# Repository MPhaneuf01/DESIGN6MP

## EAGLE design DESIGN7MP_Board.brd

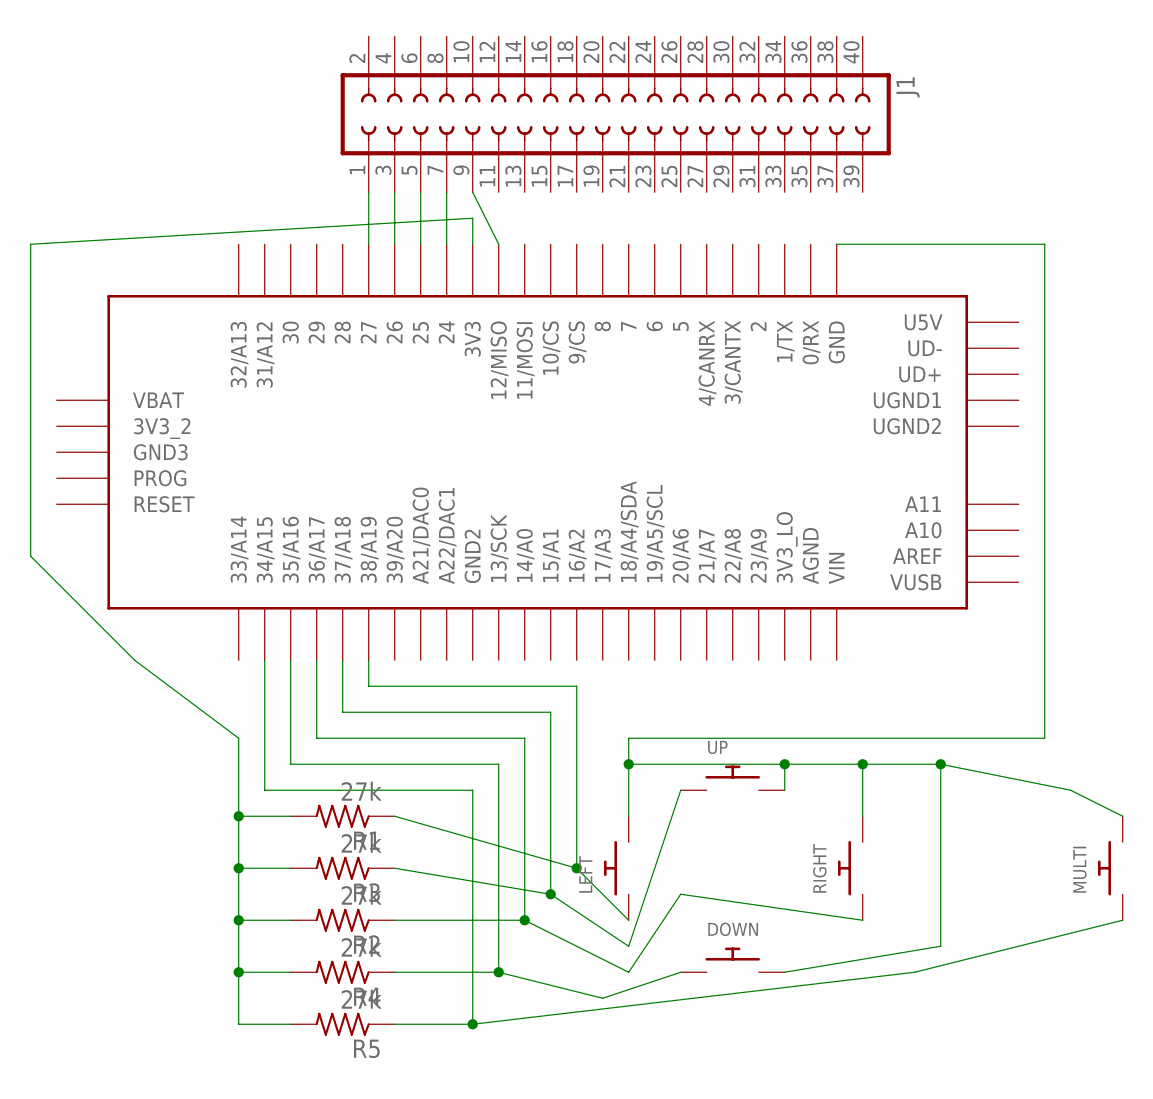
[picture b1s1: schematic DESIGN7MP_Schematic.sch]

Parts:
DOWN: SWITCH_PUSHBUTTONEVQ-PE; TACT_PANA-EVQ
J1: SOCKET-40V; S40V
LEFT: SWITCH_PUSHBUTTONEVQ-PE; TACT_PANA-EVQ
MULTI: SWITCH_PUSHBUTTONEVQ-PE; TACT_PANA-EVQ
R1, R2, R3, R4, R5: 27k; 0204/5
RIGHT: SWITCH_PUSHBUTTONEVQ-PE; TACT_PANA-EVQ
U$1: TEENSY_3.5/3.6
UP: SWITCH_PUSHBUTTONEVQ-PE; TACT_PANA-EVQ

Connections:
unnamed: R1.2, R2.2, R3.2, R4.2, R5.2, U$1.3V3
unnamed: MULTI.P$1, R5.1, U$1.34/A15
unnamed: DOWN.P$1, R4.1, U$1.35/A16
unnamed: R2.1, RIGHT.P$1, U$1.36/A17
unnamed: R3.1, U$1.37/A18, UP.P$1
unnamed: LEFT.P$1, R1.1, U$1.38/A19
unnamed: DOWN.P$2, LEFT.P$2, MULTI.P$2, RIGHT.P$2, U$1.GND, UP.P$2
unnamed: J1.9, U$1.12/MISO
unnamed: J1.7, U$1.24
unnamed: J1.5, U$1.25
unnamed: J1.3, U$1.26
unnamed: J1.1, U$1.27

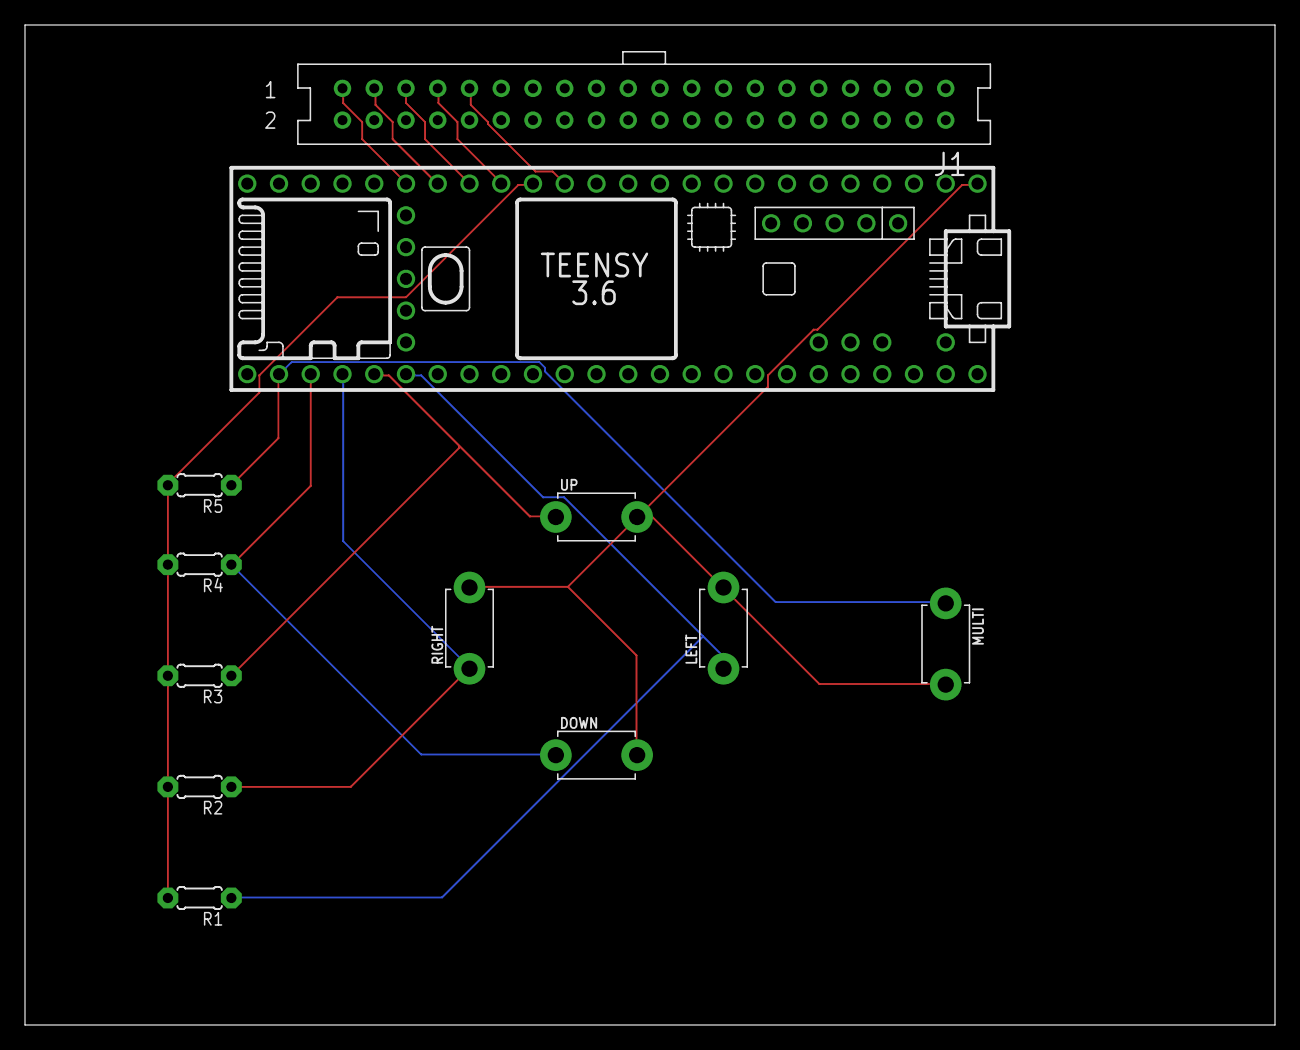
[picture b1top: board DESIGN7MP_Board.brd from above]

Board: 2 copper layers, 100.0 x 80.0 mm, 12 parts (0 on the bottom side), 12 nets.

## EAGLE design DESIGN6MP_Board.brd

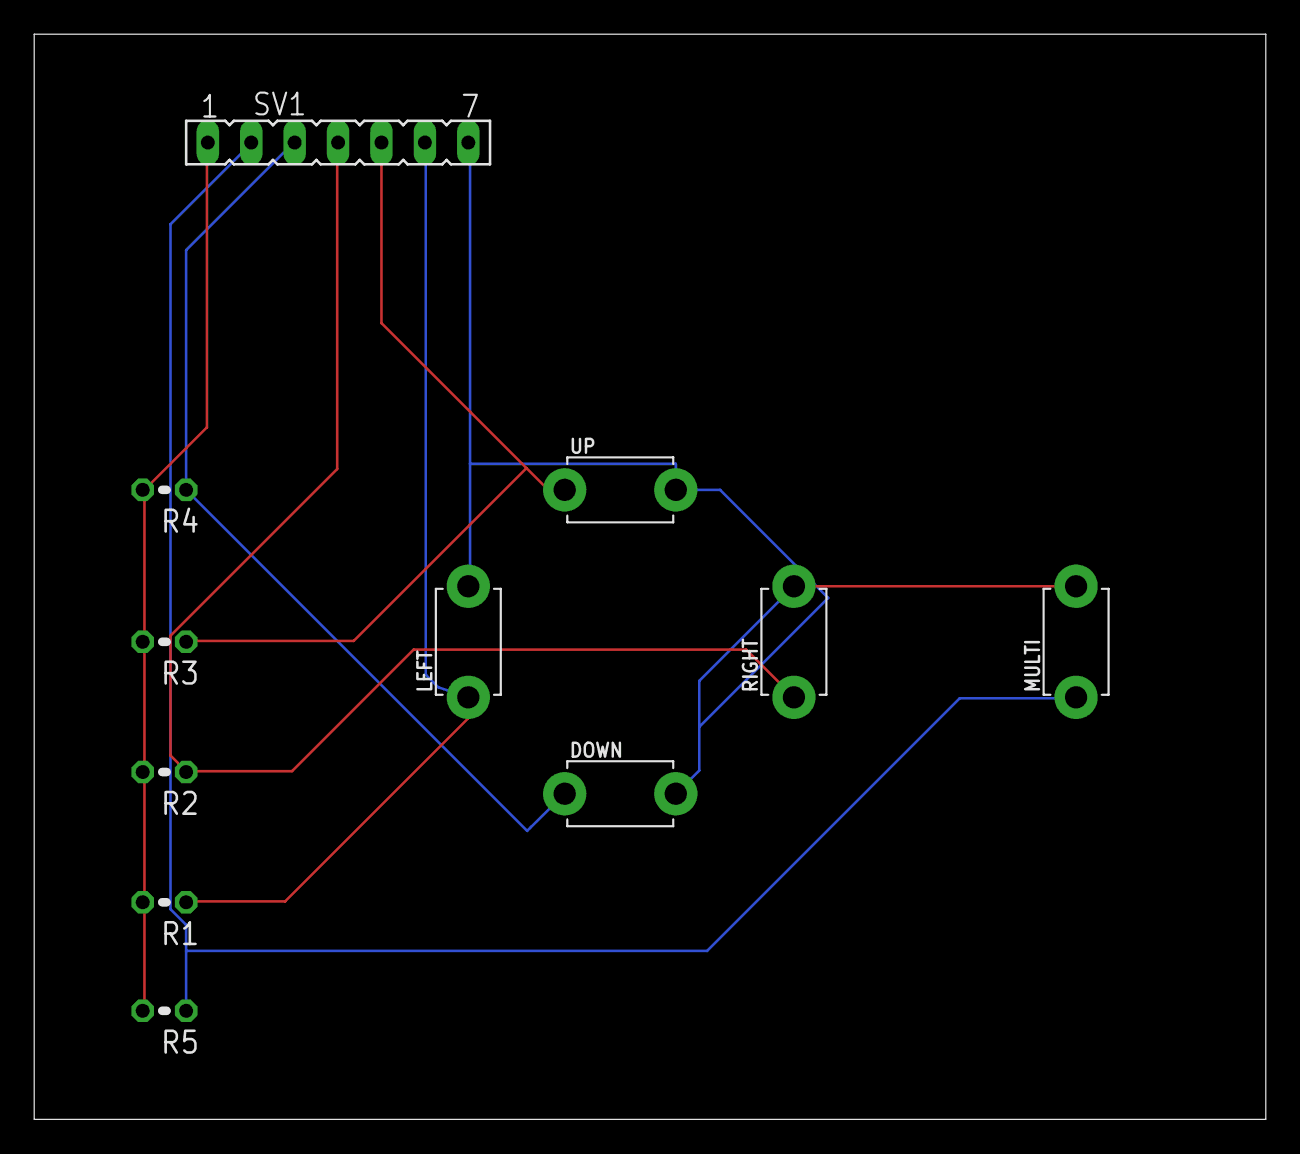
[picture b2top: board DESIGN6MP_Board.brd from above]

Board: 2 copper layers, 72.1 x 63.5 mm, 11 parts (0 on the bottom side), 7 nets.

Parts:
DOWN: TACT_PANA-EVQ
LEFT: TACT_PANA-EVQ
MULTI: TACT_PANA-EVQ
R1, R2, R3, R4, R5: 27k; 0204V
RIGHT: TACT_PANA-EVQ
SV1: FE07
UP: TACT_PANA-EVQ

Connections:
unnamed: R1.2, R2.2, R3.2, R4.2, R5.2, SV1.1
unnamed: MULTI.P$1, R5.1, SV1.2
unnamed: DOWN.P$1, R4.1, SV1.3
unnamed: R2.1, RIGHT.P$1, SV1.4
unnamed: R3.1, SV1.5, UP.P$1
unnamed: LEFT.P$1, R1.1, SV1.6
unnamed: DOWN.P$2, LEFT.P$2, MULTI.P$2, RIGHT.P$2, SV1.7, UP.P$2

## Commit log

2019-04-15 Delete DESIGN6MP_Board.brd
    Incorrect name
2019-04-15 Delete DESIGN6MP_Schematic.sch
    incorrect name
2019-04-15 Add files via upload
    Adding Correct Files
